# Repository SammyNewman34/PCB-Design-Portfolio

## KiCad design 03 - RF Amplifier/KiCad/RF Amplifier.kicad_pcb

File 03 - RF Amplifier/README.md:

# 03 - RF Amplifier (Mini-Circuits GALI-S66+)

A custom 2-layer PCB implementation of a wideband, high-linearity RF amplifier built around the **Mini-Circuits GALI-S66+** monolithic microwave integrated circuit (MMIC). Designed in **KiCad**, this board features controlled-impedance $50\ \Omega$ microstrip routing, edge-launch SMA coaxial interfaces, dual-layer ground-plane shielding, and an integrated bias-tee power network.

---

## 📂 Repository Structure

```text
03 - RF Amplifier/
├── KiCad/          # KiCad project files (.kicad_pro, .kicad_sch, .kicad_pcb)
├── Images/         # Schematic and board visualizations
│   ├── schematic.png
│   ├── pcb_2d.png
│   └── pcb_3d.png
└── README.md       # Project documentation
```

---

## 📷 Project Visuals

### Schematic Design
The schematic captures the complete RF signal chain, DC-blocking capacitors, and the bias-tee network delivering DC power to the amplifier's output pin via an RF choke.

### 2D PCB Layout
The 2D layout highlights the straight, unobstructed $50\ \Omega$ RF path from input to output alongside the top-side DC power and bias filtering network.

### 3D PCB Render
A 3D view showing the edge-launch SMA connectors sitting flush against the $1.6\text{ mm}$ board edge and the compact `SOT-89-3` placement for `U1`.

---

## 1. Circuit Overview

The GALI-S66+ is a high-dynamic-range, wideband RF gain block covering DC to $3\text{ GHz}$. Because MMIC amplifiers receive their DC bias current directly through their RF output pin, the circuit is divided into two functional stages:

1. **$50\ \Omega$ RF Signal Path (`J1` $\rightarrow$ `C2` $\rightarrow$ `U1` $\rightarrow$ `C3` $\rightarrow$ `J2`):** Amplifies incoming RF signals while isolating DC bias voltages from external test equipment or antennas.
2. **DC Bias-Tee & Power Filtering Network (`J3` $\rightarrow$ `C1` / `C4` $\rightarrow$ `R2` + `R1` $\rightarrow$ `FB1`):** Supplies regulated DC operating current to `U1` (Pin 3) while preventing high-frequency RF energy from leaking back into the power supply.

---

## 2. Bill of Materials (BOM) & Component Rationale

Every component, symbol, and KiCad footprint was selected to balance high-frequency RF signal integrity, thermal power handling, and ease of hand assembly.

| Reference | Component & Value | KiCad Symbol | KiCad Footprint | Engineering Rationale |
| :--- | :--- | :--- | :--- | :--- |
| **U1** | Mini-Circuits GALI-S66+ | `RF_Amplifier:GALI-S66` | `Package_TO_SOT_SMD:SOT-89-3` | Provides flat wideband gain across RF frequencies. The `SOT-89-3` package includes a large exposed ground/thermal tab on Pin 2 for low-inductance grounding and heat dissipation. |
| **J1, J2** | Edge-Launch SMA Connectors ($50\ \Omega$) | `Connector:Conn_Coaxial` | `Connector_Coaxial:SMA_Amphenol_132289_EdgeMount` | Upgraded from SMB to standard SMA for superior mechanical durability and broader test-equipment compatibility. Designed to straddle a standard $1.6\text{ mm}$ PCB edge so coaxial cables mate parallel to the board plane. |
| **J3** | 2-Pin DC Power Terminal | `Connector:Screw_Terminal_01x02` | `TerminalBlock_Phoenix:TerminalBlock_Phoenix_MKDS-1,5-2_1x02_P5.00mm_Horizontal` | Standard $5.00\text{ mm}$ pitch screw terminal allows secure, tool-assisted connection of bench power supply leads without accidental pull-outs. |
| **C2, C3** | $22\text{ nF}$ DC-Blocking Capacitors | `Device:C` | `Capacitor_SMD:C_0603_1608Metric` | Blocks DC bias voltage from reaching `J1` and `J2`. The compact imperial `0603` (`1608Metric`) package minimizes parasitic series inductance and physical width discontinuities along the $50\ \Omega$ RF transmission line. |
| **C4** | $10\text{ nF}$ High-Frequency Bypass Cap | `Device:C` | `Capacitor_SMD:C_0603_1608Metric` | Shunts residual high-frequency RF noise on the DC bias rail directly to ground. Sized at `0603` (`1608Metric`) for low self-inductance and reliable DRC pad clearance. |
| **C1** | $100\ \mu\text{F}$ Bulk Decoupling Cap | `Device:C_Polarized` | `Capacitor_SMD:CP_Elec_6.3x5.4` | Bulk electrolytic capacitor that smooths low-frequency power supply ripple and transient current demands at the DC input connector. |
| **R1, R2** | $150\ \Omega$ Bias Resistors ($\times 2$) | `Device:R` | `Resistor_SMD:R_0805_2012Metric` | Placed in series to provide $300\ \Omega$ total bias resistance (ideal for $\sim 9\text{ V}$–$12\text{ V}$ supply operation at $\sim 50$–$65\text{ mA}$). Splitting the resistance across two `0805` packages safely distributes $\sim 0.2$–$0.3\text{ W}$ of heat dissipation across both resistors. |
| **FB1** | Ferrite Bead / RF Choke | `Device:FerriteBead` | `Inductor_SMD:L_0805_2012Metric` | Acts as a high-impedance RF choke at operating frequencies while passing DC bias current into Pin 3 (`OUT`) with minimal voltage drop. The `0805` package comfortably handles the DC bias current without saturating. |

---

## 3. PCB Layout & RF Design Decisions

* **Board Stackup & Controlled Impedance:** Designed for a standard 2-layer **$1.6\text{ mm}$ FR4** substrate with `F.Cu` carrying signal traces and `B.Cu` acting as a continuous ground reference plane. RF traces between `J1`, `C2`, `U1`, `C3`, and `J2` are routed as straight, direct $50\ \Omega$ microstrip lines ($\sim 3.0\text{ mm}$ width) with no $90^\circ$ bends or via transitions to prevent impedance reflections.
* **Dual-Layer Ground Pour & Via Stitching:** Both top (`F.Cu`) and bottom (`B.Cu`) layers are flooded with solid `GND` copper pours. Ground vias are offset slightly from component pads (avoiding co-located via-in-pad drill conflicts) to stitch the top and bottom reference planes together and provide a low-inductance return path for `U1`.
* **Edge-Launch Alignment:** The `Edge.Cuts` board boundary bisects the mounting tabs of `J1` and `J2` so the SMA center pins and ground legs sit flush against the top and bottom copper surfaces.
* **Silkscreen Hygiene:** Overlapping footprint value strings and redundant library labels were hidden on `F.SilkS`, leaving clean, legible reference designators (`U1`, `C1`–`C4`, `R1`–`R2`, `FB1`, `J1`–`J3`) for assembly.

---

## 4. Fabrication & Assembly Notes

1. **Gerber Generation:** Exported standard RS-274X Gerber layers (`F.Cu`, `B.Cu`, `F.Mask`, `B.Mask`, `F.SilkS`, `B.SilkS`, `Edge.Cuts`) alongside Excellon drill files (`.drl`), verified with zero Design Rules Checker (DRC) violations.
2. **Board Specs for Ordering:**
   * **Layers:** 2
   * **Thickness:** $1.6\text{ mm}$
   * **Material:** FR-4 ($\varepsilon_r \approx 4.4 - 4.6$)
   * **Copper Weight:** $1\text{ oz}$ ($35\ \mu\text{m}$)
3. **Power Supply Polarity:** Double-check polarity at screw terminal `J3` (Pin 1 = `+VCC`, Pin 2 = `GND`) before applying power, as `C1` and `U1` are polarity-sensitive.

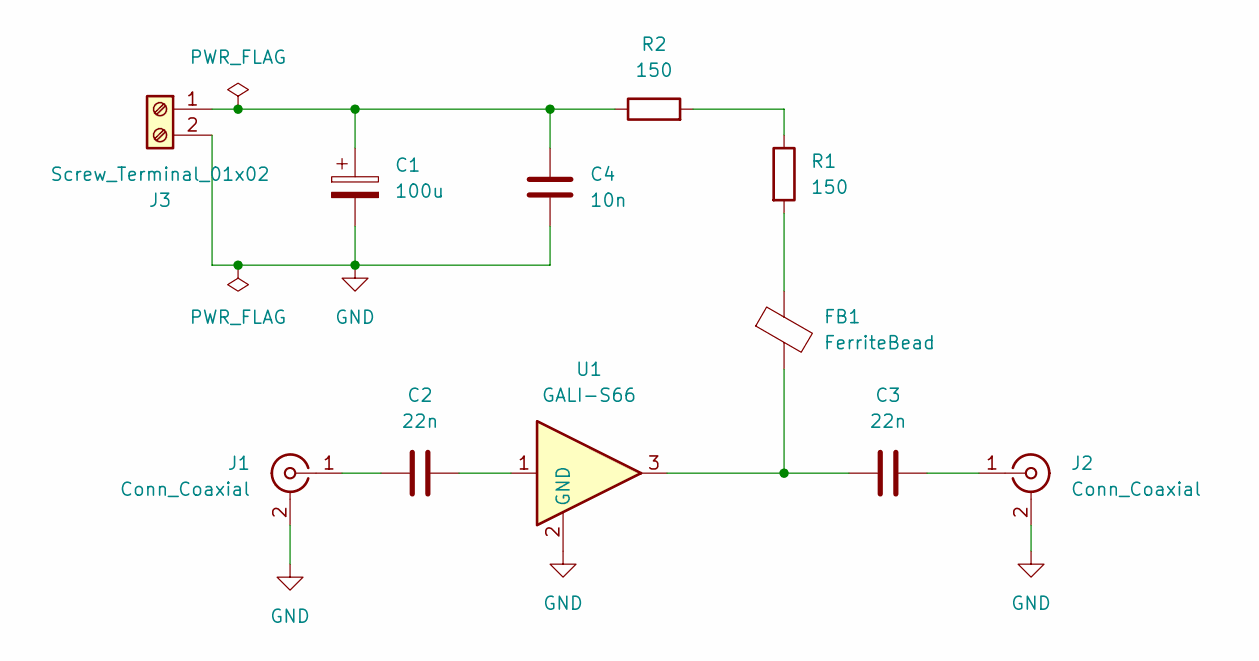
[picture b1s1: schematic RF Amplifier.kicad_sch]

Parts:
C1: 100u; CP_Radial_D6.3mm_P2.50mm
C2, C3: 22n; C_0603_1608Metric
C4: 10n; C_0603_1608Metric
FB1: FerriteBead; L_0805_2012Metric
J1, J2: Conn_Coaxial; SMA_Amphenol_132289_EdgeMount
J3: Screw_Terminal_01x02; TerminalBlock_Phoenix_MKDS-1,5-2_1x02_P5.00mm_Horizontal
R1, R2: 150; R_0805_2012Metric
U1: GALI-S66; SOT-89-3

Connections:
GND: C1.2, C4.2, J1.2 (Ext), J2.2 (Ext), J3.2, U1.2 (GND_2)
unnamed: C2.2, U1.1
unnamed: C3.1, FB1.2, U1.3
unnamed: FB1.1, R1.2
unnamed: C2.1, J1.1 (In)
unnamed: C3.2, J2.1 (In)
unnamed: C1.1, C4.1, J3.1, R2.1
unnamed: R1.1, R2.2

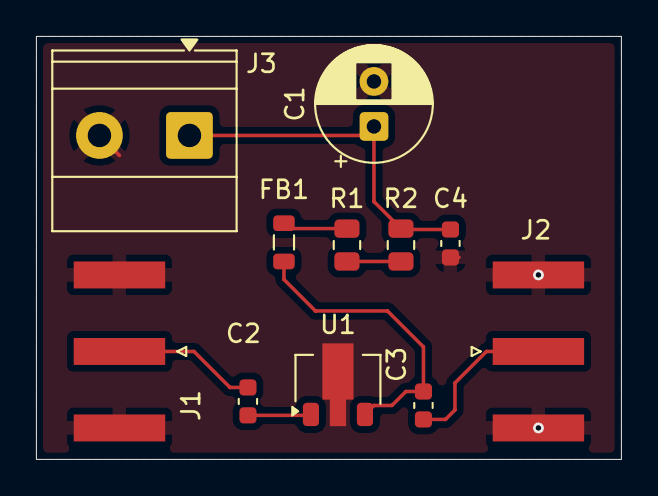
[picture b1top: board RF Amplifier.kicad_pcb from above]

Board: 2 copper layers, 32.5 x 23.5 mm, 11 parts (0 on the bottom side), 8 nets.

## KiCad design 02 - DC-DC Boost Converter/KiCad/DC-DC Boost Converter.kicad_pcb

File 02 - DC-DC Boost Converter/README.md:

# DC-DC Boost Converter

## Overview

An **XL6009-based DC-DC boost converter** designed in KiCad from schematic through PCB layout and 3D visualization.

The circuit is based on the typical boost converter application circuit provided in the **XL6009 datasheet**. The reference circuit was used as the starting point, with the components selected and the complete schematic, PCB layout, and 3D model developed in KiCad.

### Project Workflow

- Created the schematic in KiCad
- Selected and assigned component footprints
- Added a custom XL6009 symbol, footprint, and 3D model
- Designed the PCB layout
- Added thermal vias around the XL6009 for improved heat dissipation
- Added a 3D model for the DR125 inductor
- Created the complete 3D PCB visualization
- Ran Electrical Rules Check (ERC)
- Ran Design Rules Check (DRC)

---

## Design Specifications

| Parameter | Value |
|---|---|
| Converter Type | DC-DC Boost Converter |
| Switching Regulator | XL6009 |
| Reference Input Range | 12–16 V |
| Target Output Voltage | ~18.5 V |
| Inductor | 33 µH / 4 A |
| Schottky Diode | SS34 |
| Input Bulk Capacitor | 47 µF / 50 V |
| Input Ceramic Capacitor | 1 µF |
| Output Bulk Capacitor | 220 µF / 50 V |
| Output Ceramic Capacitor | 1 µF |
| Feedback Resistor | 1 kΩ |
| Feedback Resistance | 13.8 kΩ |
| PCB Design Software | KiCad |

The input voltage range and target output voltage are based on the XL6009 datasheet reference design.

---

## How a Boost Converter Works

A boost converter is a switching DC-DC converter that produces an output voltage higher than its input voltage.

The XL6009 controls the switching process. Energy is temporarily stored in the inductor and then transferred to the output at a higher voltage.

The conversion process can be understood in two main stages.

### 1. Switch ON

When the internal switch in the XL6009 turns ON, current flows from the input supply through the inductor.

The inductor stores energy in its magnetic field.

During this portion of the switching cycle, the Schottky diode prevents the output capacitor from discharging back toward the switching node.

### 2. Switch OFF

When the internal switch turns OFF, the magnetic field in the inductor collapses.

The inductor generates a voltage that adds to the input voltage, causing current to flow through the Schottky diode toward the output.

The output capacitors store this energy and help maintain a stable DC output voltage.

The XL6009 rapidly repeats these switching cycles to transfer energy from the input to the output and increase the voltage.

---

## Circuit Operation

The main power path of the converter is:

VIN → L1 → Switching Node → D1 → VOUT

The XL6009 controls the switching node while L1 stores and releases energy during each switching cycle.

D1 provides the path from the inductor to the output when the internal switch turns OFF.

The output capacitors then filter the resulting switching waveform into a DC output.

---

## Output Voltage Feedback

The XL6009 regulates the output voltage using its **FB (feedback) pin**.

A resistor divider is connected between VOUT and GND:

             VOUT
               |
              RV1
             13.8 kΩ
               |
               +------ FB
               |
              R1
             1 kΩ
               |
              GND

The XL6009 uses the voltage at the FB pin to regulate the switching operation.

The datasheet provides the following relationship:

VOUT = 1.25 × (1 + R2/R1)

Using the selected values:

R1 = 1 kΩ
R2 = 13.8 kΩ

VOUT = 1.25 × (1 + 13.8 kΩ / 1 kΩ)

VOUT ≈ 18.5 V

The feedback network therefore sets the target output voltage to approximately **18.5 V**.

---

## Component Selection

### XL6009

The **XL6009** is the main switching regulator in the circuit.

It controls the switching operation required to transfer energy through the inductor and regulate the output voltage.

A custom KiCad symbol, PCB footprint, and 3D model were added to the project.

The custom XL6009 files are included in the project repository so that the design does not depend on the original local library files.

---

### L1 — 33 µH / 4 A Inductor

The inductor is the primary energy-storage component in the boost converter.

When the XL6009's internal switch is ON, current flows through L1 and energy is stored in its magnetic field.

When the switch turns OFF, the stored energy is released toward the output through the Schottky diode.

The selected inductor is rated for approximately 4 A according to the reference design.

A **DR125 3D model** was also included for the PCB's 3D visualization.

---

### D1 — SS34 Schottky Diode

The SS34 is a Schottky diode used to transfer energy from the inductor to the output.

Schottky diodes are commonly used in switching converters because of their relatively low forward voltage and fast switching characteristics.

The diode also prevents the output from discharging back toward the switching node when the XL6009's internal switch is ON.

---

### R1 and RV1 — Feedback Network

R1 and RV1 form the feedback voltage divider used to control the output voltage.

- R1 = 1 kΩ
- RV1 = 13.8 kΩ

The resulting feedback voltage is monitored by the XL6009 through its FB pin.

---

### C1 — 47 µF / 50 V Input Capacitor

C1 is the main input bulk capacitor.

It helps stabilize the input supply and reduces voltage fluctuations caused by the switching current drawn by the converter.

The 50 V rating also provides voltage margin above the intended input range.

---

### C2 — 1 µF Input Capacitor

C2 provides additional high-frequency filtering on the input side.

The smaller capacitor complements the larger bulk capacitor by helping filter higher-frequency switching components.

---

### C3 — 1 µF Output Capacitor

C3 provides additional high-frequency filtering on the output.

It works together with the larger output capacitor to reduce high-frequency voltage ripple.

---

### C4 — 220 µF / 50 V Output Capacitor

C4 is the main output bulk capacitor.

It stores energy delivered by the converter and helps reduce output-voltage ripple and fluctuations.

---

## PCB Layout Considerations

Because the XL6009 operates as a switching regulator, PCB layout is an important part of the design.

The PCB layout was developed with consideration for:

- Short current paths around the switching circuitry
- Placement of the inductor and Schottky diode near the XL6009
- Adequate copper area for higher-current connections
- Ground copper areas
- Input and output capacitor placement
- Appropriate trace clearances
- Thermal management around the XL6009

The completed PCB was checked using KiCad's Design Rules Checker (DRC).

---

## Thermal Management

The XL6009 is the primary switching device and can dissipate heat during operation.

**Thermal vias were added around the XL6009 on the PCB to provide an additional path for heat to spread into the PCB copper.**

The copper areas and thermal vias help distribute heat away from the regulator and improve the PCB's ability to dissipate heat.

The thermal-via implementation was included as part of the PCB layout rather than relying only on the component package for heat dissipation.

---

## Schematic

The schematic was developed in KiCad using the XL6009 datasheet reference circuit as the starting point.

---

## PCB Layout

The PCB was designed and routed in KiCad.

---

## 3D Visualization

A 3D model was created to visualize the completed PCB and component placement.

Custom 3D models were included for components that were not available in the standard KiCad libraries.

---

## Design Verification

### Electrical Rules Check (ERC)

KiCad's Electrical Rules Checker (ERC) was run on the completed schematic to identify potential electrical connection and schematic-rule issues.

### Design Rules Check (DRC)

KiCad's Design Rules Checker (DRC) was run on the completed PCB layout to check PCB design constraints including:

- Trace clearances
- Connectivity
- Unconnected items
- PCB design-rule violations

---

## Custom KiCad Libraries and Models

The project includes the custom files required for the XL6009 and the PCB 3D visualization.

### XL6009

The `XL6009` folder contains:

- Custom schematic symbol
- Custom PCB footprint
- Custom 3D model

These files are included with the project so that the custom XL6009 component can be retained when the project is opened on another computer.

### DR125 Inductor

The project also includes the `DR125.STEP` 3D model used to represent the 33 µH inductor in KiCad's 3D Viewer.

---

## Tools Used

- **KiCad**
- XL6009 datasheet
- KiCad Schematic Editor
- KiCad PCB Editor
- KiCad 3D Viewer

---

## Project Files

The `KiCad` directory contains the complete KiCad project, including:

- Schematic
- PCB layout
- KiCad project configuration
- Custom XL6009 symbol
- Custom XL6009 footprint
- Custom XL6009 3D model
- DR125 inductor 3D model

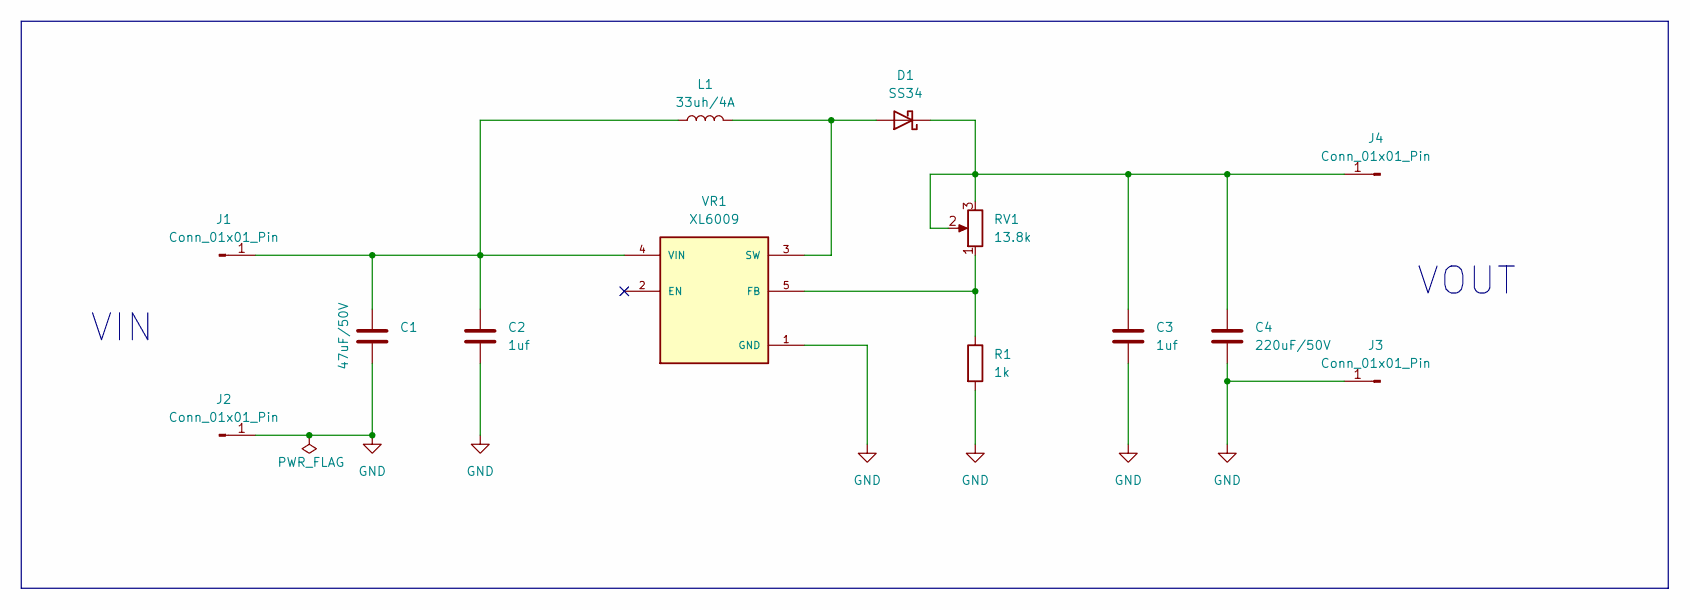
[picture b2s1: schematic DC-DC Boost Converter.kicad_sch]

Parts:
C1: 47uF/50V; C_Radial_D6.3mm_H11.0mm_P2.50mm
C2, C3: 1uf; C_0805_2012Metric
C4: 220uF/50V; C_Radial_D6.3mm_H11.0mm_P2.50mm
D1: SS34; D_SMA
J1, J2, J3, J4: Conn_01x01_Pin; PinHeader_1x01_P2.54mm_Vertical
L1: 33uh/4A; L_12x12mm_H8mm
R1: 1k; R_1206_3216Metric
RV1: 13.8k; Potentiometer_Bourns_3296W_Vertical
VR1: XL6009; DPAK170P1435X465-6N; PARTREV 1.1

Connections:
GND: C1.2, C2.2, C3.2, C4.2, J2.1 (Pin_1_1), J3.1 (Pin_1_1), R1.2, VR1.1 (GND)
unnamed: D1.2 (A), L1.2, VR1.3 (SW), VR1.6 (SW)
unnamed: C3.1, C4.1, D1.1 (K), J4.1 (Pin_1_1), RV1.2, RV1.3
unnamed: C1.1, C2.1, J1.1 (Pin_1_1), L1.1, VR1.4 (VIN)
unnamed: R1.1, RV1.1, VR1.5 (FB)

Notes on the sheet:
VIN
VOUT

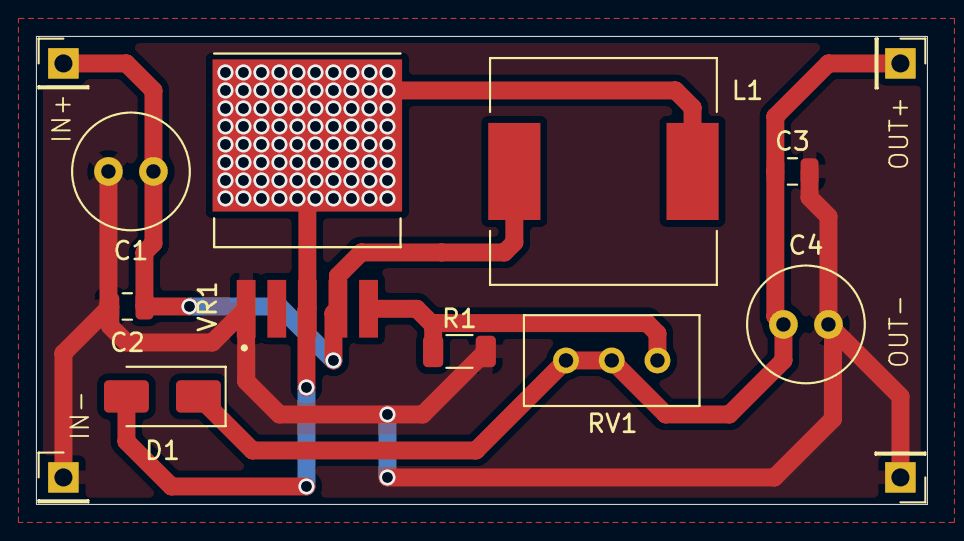
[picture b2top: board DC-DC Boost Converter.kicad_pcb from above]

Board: 2 copper layers, 49.5 x 26.0 mm, 13 parts (0 on the bottom side), 5 nets.

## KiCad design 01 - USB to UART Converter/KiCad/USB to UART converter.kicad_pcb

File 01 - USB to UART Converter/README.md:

# USB to UART Converter with CP2102

## Overview

A USB to UART converter PCB designed in **KiCad** using the Silicon Labs CP2102 USB-to-UART bridge IC.

This project was completed as a hands-on PCB design exercise based on the *Master KiCad with Projects* YouTube tutorial series. The project provided practical experience with schematic capture, component selection, PCB layout, component placement, routing, and design-rule checking.

## Project Goals

* Design a USB-to-UART interface using the CP2102
* Create the complete schematic in KiCad
* Select and connect the required supporting components
* Design a compact PCB layout
* Practice component placement and signal routing
* Create a complete, organized KiCad project suitable for PCB fabrication

## Tools

* **KiCad**
* **CP2102 USB-to-UART bridge**

## Design Process

### 1. Schematic Design

The circuit schematic was created in KiCad, including the CP2102 and its required supporting components for USB-to-UART communication.

### 2. PCB Layout

The schematic was transferred to the PCB editor, where components were placed and the electrical connections were routed.

### 3. 3D Visualization

KiCad's 3D viewer was used to inspect the completed PCB layout and component placement.

## Skills Practiced

* Schematic capture
* Component selection
* PCB component placement
* PCB routing
* Signal routing
* PCB layout optimization
* Design Rule Checking (DRC)
* KiCad project organization
* USB/UART interface fundamentals

## Project Files

The `KiCad` folder contains the original KiCad project files:

* `.kicad_pro` — KiCad project configuration
* `.kicad_sch` — Schematic
* `.kicad_pcb` — PCB layout

## Reference

This project was based on the following tutorial:

**Master KiCad with Projects — USB to UART Converter with CP2102**

YouTube tutorial series: *Master KiCad with Projects*

## Project Status

**Completed — PCB design finished. DRC checks and edits in proccess**

This project was created as a learning exercise. Future versions may include design modifications, fabrication, assembly, and functional testing of the completed board.

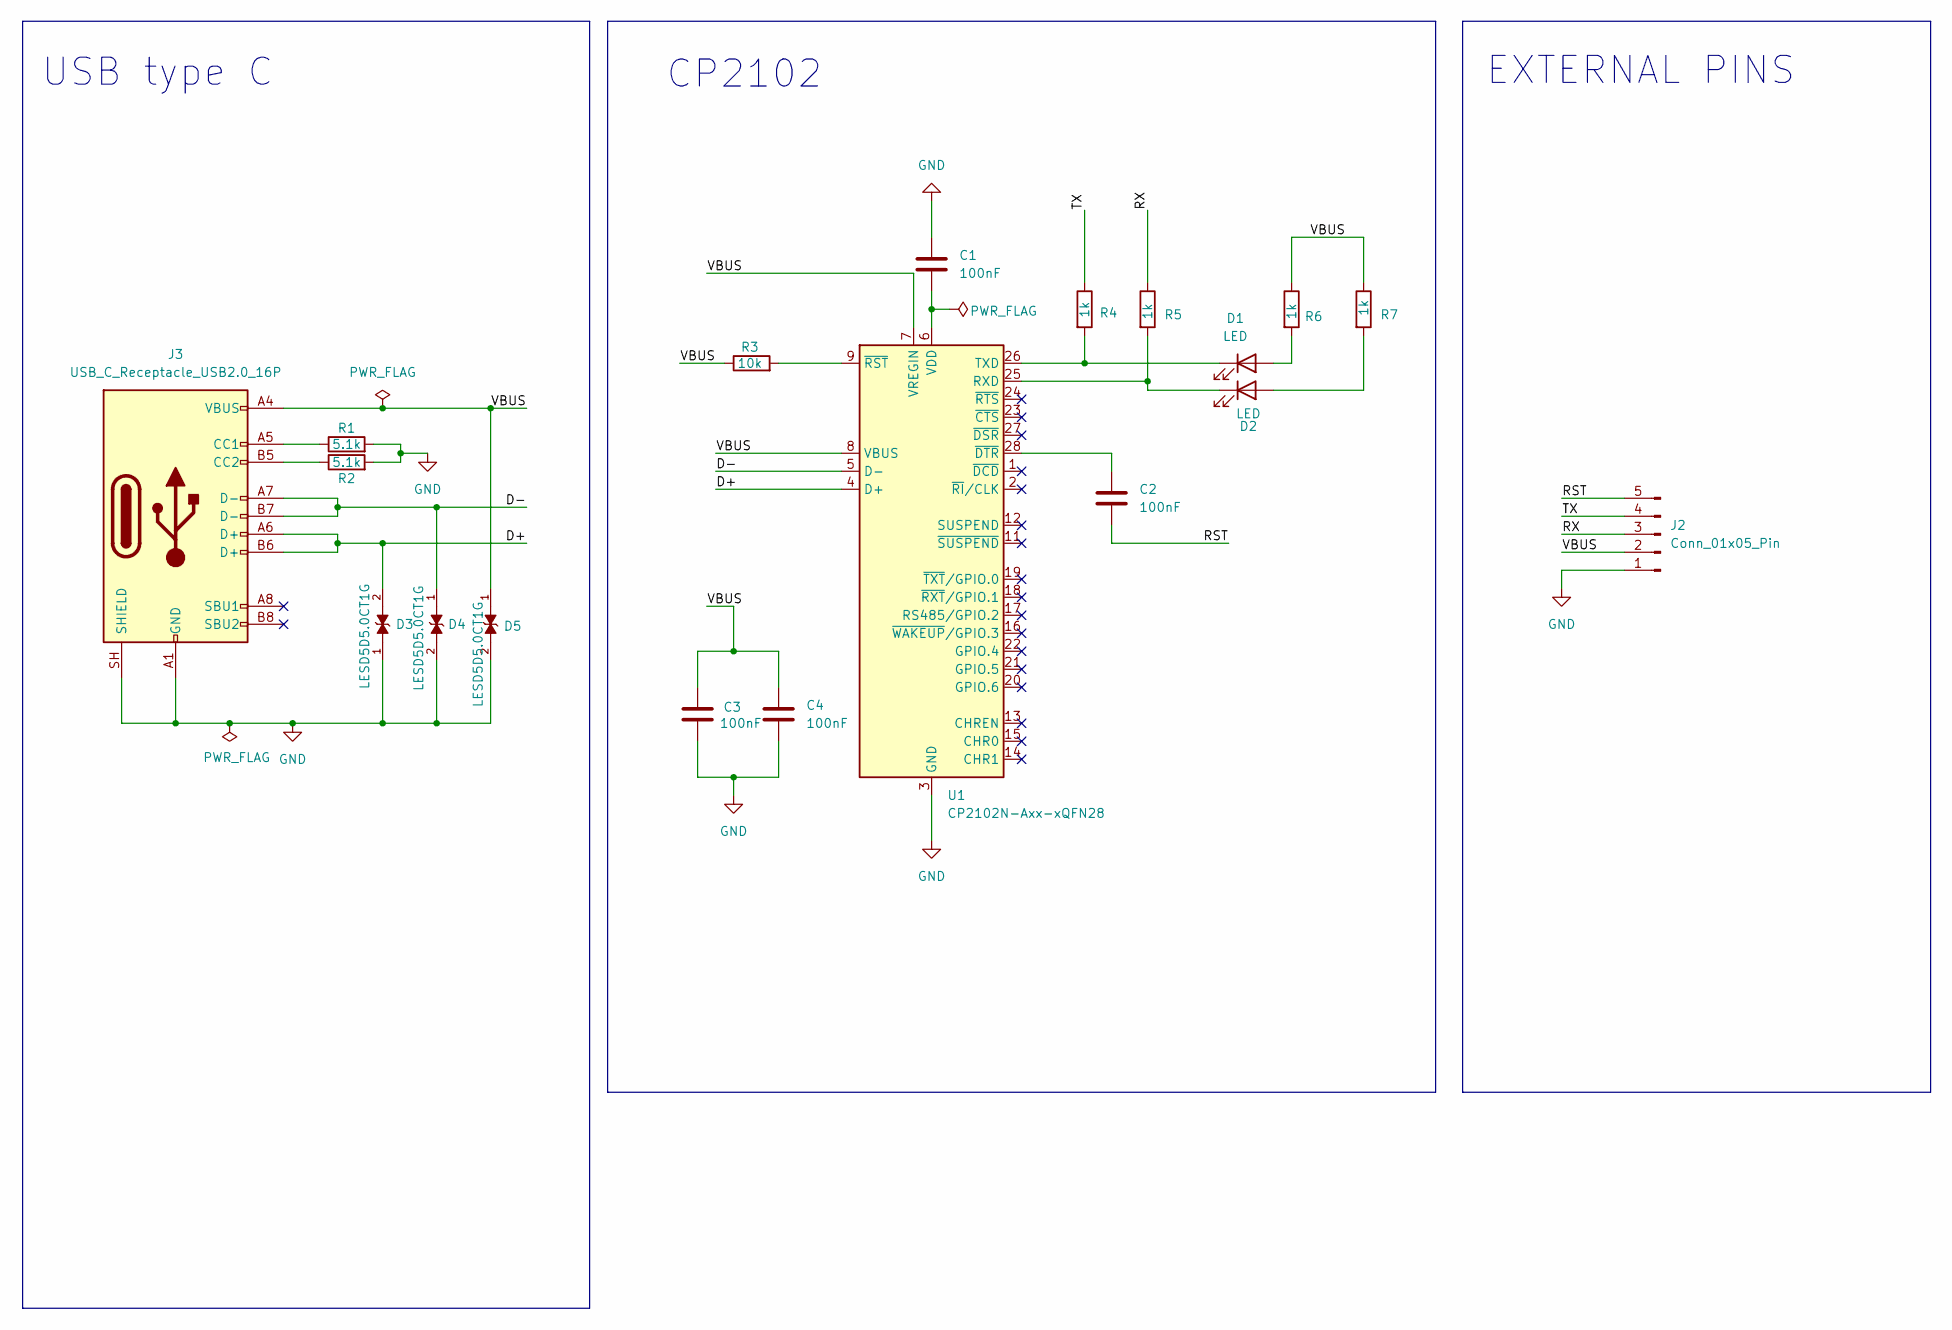
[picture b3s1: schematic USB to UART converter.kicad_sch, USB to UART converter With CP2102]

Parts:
C1, C2, C3, C4: 100nF; C_0201_0603Metric
D1, D2: LED; LED_0402_1005Metric
D3, D4, D5: LESD5D5.0CT1G; TVS_LESD5D5.0CT1G; PARTREV O
J2: Conn_01x05_Pin; PinHeader_1x05_P2.54mm_Horizontal
J3: USB_C_Receptacle_USB2.0_16P; USB_C_Receptacle_HRO_TYPE-C-31-M-12
R1, R2: 5.1k; R_0201_0603Metric
R3: 10k; R_0201_0603Metric
R4, R5, R6, R7: 1k; R_0201_0603Metric
U1: CP2102N-Axx-xQFN28; QFN-28-1EP_5x5mm_P0.5mm_EP3.35x3.35mm

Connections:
/D+: D3.2, J3.A6 (D+), J3.B6 (D+), U1.4 (D+)
/D-: D4.1, J3.A7 (D-), J3.B7 (D-), U1.5 (D-)
/RST: C2.2, J2.5
/RX: J2.3, R5.1
/TX: J2.4, R4.1
/VBUS: C3.1, C4.1, D5.1, J2.2, J3.A4 (VBUS), J3.A9 (VBUS), J3.B4 (VBUS), J3.B9 (VBUS), R3.1, R6.1, R7.1, U1.7 (VREGIN), U1.8 (VBUS)
GND: C1.1, C3.2, C4.2, D3.1, D4.2, D5.2, J2.1, J3.A1 (GND), J3.A12 (GND), J3.B1 (GND), J3.B12 (GND), J3.SH (SHIELD), R1.2, R2.2, U1.3 (GND), U1.29 (GND)
unnamed: D1.2 (A), R6.2
unnamed: D1.1 (K), R4.2, U1.26 (TXD)
unnamed: D2.2 (A), R7.2
unnamed: D2.1 (K), R5.2, U1.25 (RXD)
unnamed: J3.A5 (CC1), R1.1
unnamed: J3.B5 (CC2), R2.1
unnamed: C1.2, U1.6 (VDD)
unnamed: C2.1, U1.28 (~DTR)
unnamed: R3.2, U1.9 (~RST)

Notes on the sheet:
CP2102
USB type C
EXTERNAL PINS

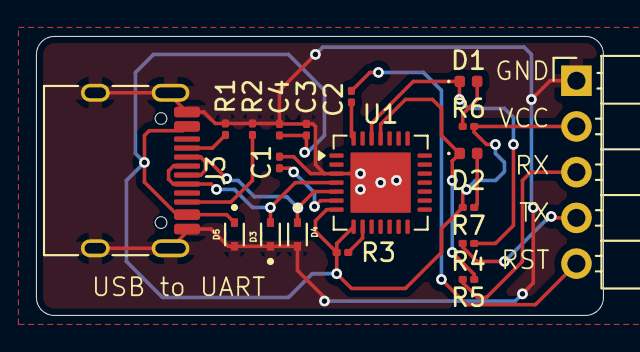
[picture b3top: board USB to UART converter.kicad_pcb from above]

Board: 2 copper layers, 31.5 x 15.5 mm, 19 parts (0 on the bottom side), 16 nets.
